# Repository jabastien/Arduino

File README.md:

# Arduino
This GitHub repo is dedicated to Arduino projects.

<H1>
https://www.arduino.cc/
<H1>

<h3>
https://www.arduino.cc/en/Reference/HomePage
</h3>

<h3>Artificial Candle</h3>
https://create.arduino.cc/projecthub/laserbrain/arduino-controlled-artificial-candle-lights-65a46d

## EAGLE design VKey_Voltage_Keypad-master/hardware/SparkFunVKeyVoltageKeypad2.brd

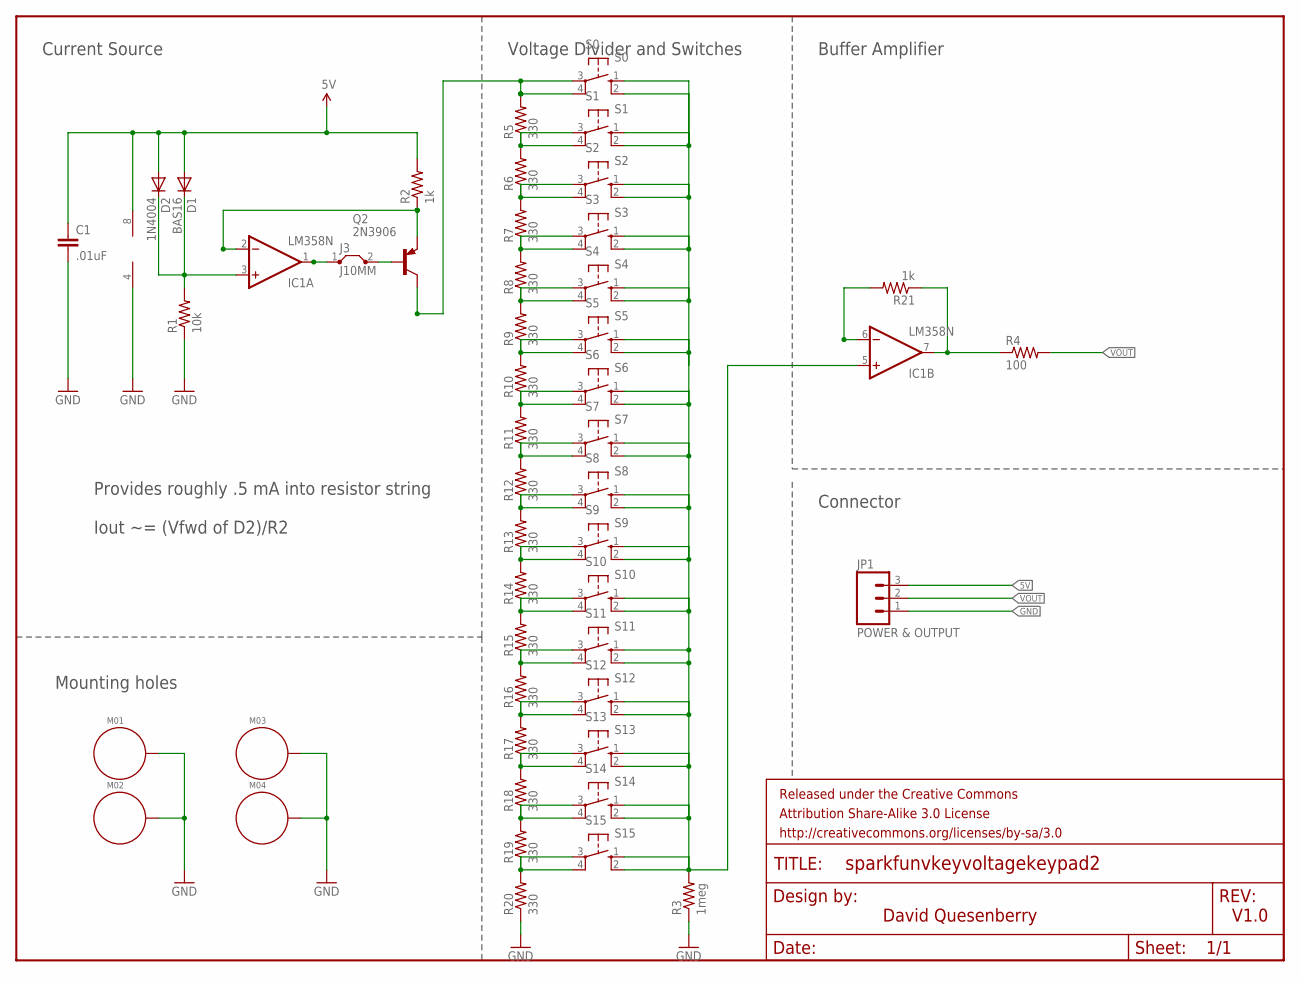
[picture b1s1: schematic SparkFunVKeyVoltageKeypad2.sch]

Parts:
C1: .01uF; 0603-CAP
D1: BAS16; SOD-323
D2: 1N4004; DO41-10
FRAME1: FRAME-LETTER; CREATIVE_COMMONS
IC1: LM358N; DIL08
J3: J10MM; 10
JP1: POWER & OUTPUT; 1X03_NO_SILK
M01, M02, M03, M04: STANDOFF_ELECTRICAL; STANDOFF-ELECTRICAL
Q2: 2N3906; TO92
R1: 10k; 0603-RES
R2, R21: 1k; 0603-RES
R3: 1meg; 0603-RES
R4: 100; 0603-RES
R5, R6, R7, R8, R9, R10, R11, R12, R13, R14, R15, R16, R17, R18, R19, R20: 330; 0603-RES
S0: S0; B3F-10XX
S1: S1; B3F-10XX
S2: S2; B3F-10XX
S3: S3; B3F-10XX
S4: S4; B3F-10XX
S5: S5; B3F-10XX
S6: S6; B3F-10XX
S7: S7; B3F-10XX
S8: S8; B3F-10XX
S9: S9; B3F-10XX
S10: S10; B3F-10XX
S11: S11; B3F-10XX
S12: S12; B3F-10XX
S13: S13; B3F-10XX
S14: S14; B3F-10XX
S15: S15; B3F-10XX

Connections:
5V: C1.1, D1.2 (A), D2.A, IC1.8 (V+), JP1.3, R2.2
GND: C1.2, IC1.4 (V-), JP1.1, M01.P1, M02.P1, M03.P1, M04.P1, R1.1, R3.1, R20.1
unnamed: D1.1 (C), D2.C, IC1.3 (+IN), R1.2
unnamed: J3.2, Q2.2 (B)
unnamed: IC1.5 (+IN), R3.2, S0.1 (S), S0.2 (S1), S1.1 (S), S1.2 (S1), S2.1 (S), S2.2 (S1), S3.1 (S), S3.2 (S1), S4.1 (S), S4.2 (S1), S5.1 (S), S5.2 (S1), S6.1 (S), S6.2 (S1), S7.1 (S), S7.2 (S1), S8.1 (S), S8.2 (S1), S9.1 (S), S9.2 (S1), S10.1 (S), S10.2 (S1), S11.1 (S), S11.2 (S1), S12.1 (S), S12.2 (S1), S13.1 (S), S13.2 (S1), S14.1 (S), S14.2 (S1), S15.1 (S), S15.2 (S1)
unnamed: R14.1, R15.2, S10.3, S10.4 (P1)
unnamed: IC1.2 (-IN), Q2.3 (E), R2.1
unnamed: Q2.1 (C), R5.2, S0.3, S0.4 (P1)
unnamed: R5.1, R6.2, S1.3, S1.4 (P1)
unnamed: R6.1, R7.2, S2.3, S2.4 (P1)
unnamed: R7.1, R8.2, S3.3, S3.4 (P1)
unnamed: R8.1, R9.2, S4.3, S4.4 (P1)
unnamed: R9.1, R10.2, S5.3, S5.4 (P1)
unnamed: R10.1, R11.2, S6.3, S6.4 (P1)
unnamed: R11.1, R12.2, S7.3, S7.4 (P1)
unnamed: R12.1, R13.2, S8.3, S8.4 (P1)
unnamed: R13.1, R14.2, S9.3, S9.4 (P1)
unnamed: R19.1, R20.2, S15.3, S15.4 (P1)
unnamed: IC1.7 (OUT), R4.1, R21.1
unnamed: IC1.6 (-IN), R21.2
unnamed: R15.1, R16.2, S11.3, S11.4 (P1)
unnamed: R16.1, R17.2, S12.3, S12.4 (P1)
unnamed: R17.1, R18.2, S13.3, S13.4 (P1)
unnamed: R18.1, R19.2, S14.3, S14.4 (P1)
unnamed: IC1.1 (OUT), J3.1
VOUT: JP1.2, R4.2

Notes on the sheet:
V1.0
Current Source
Buffer Amplifier
Mounting holes
Voltage Divider and Switches
Connector
Provides roughly .5 mA into resistor string
Iout ~= (Vfwd of D2)/R2
David Quesenberry

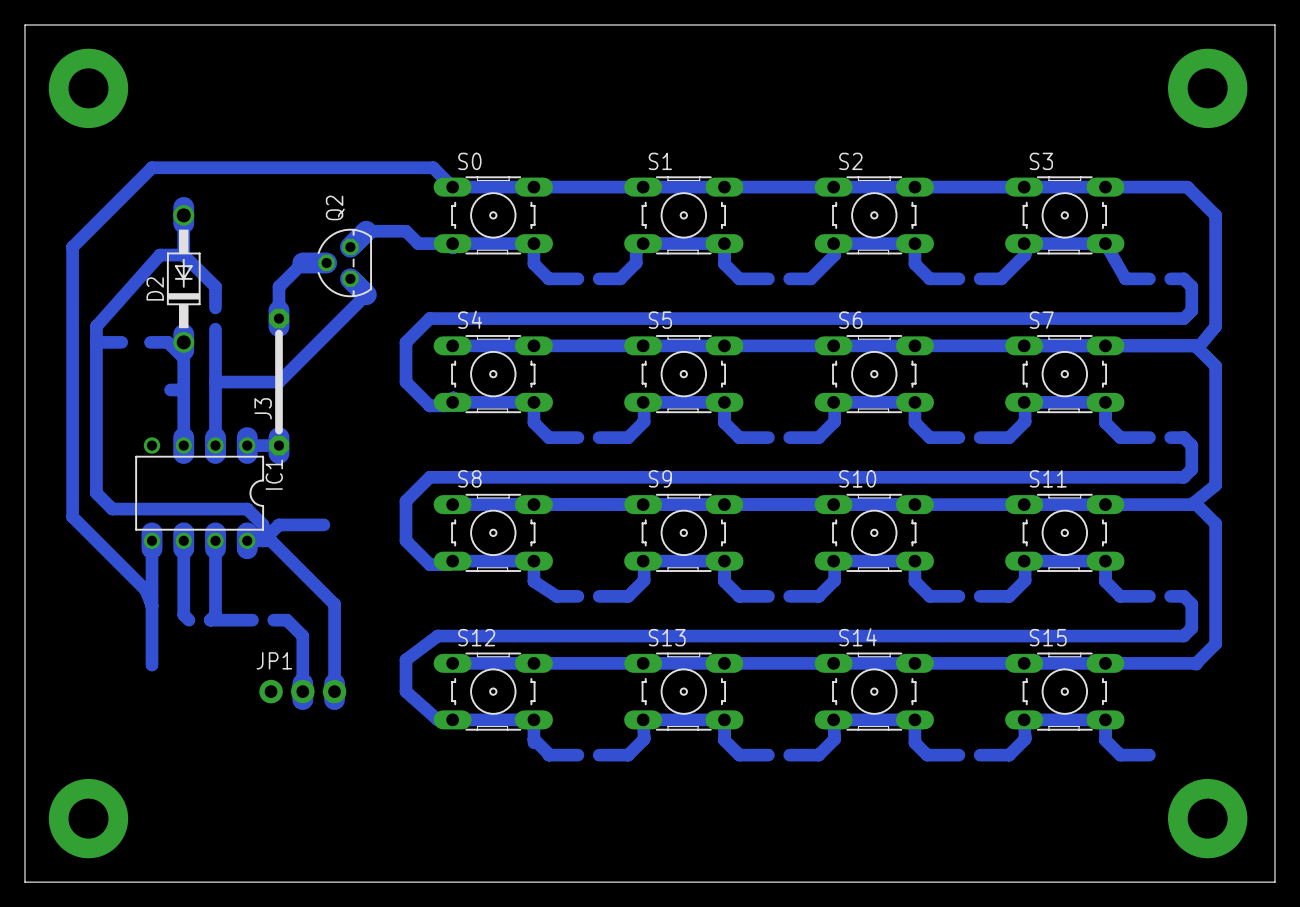
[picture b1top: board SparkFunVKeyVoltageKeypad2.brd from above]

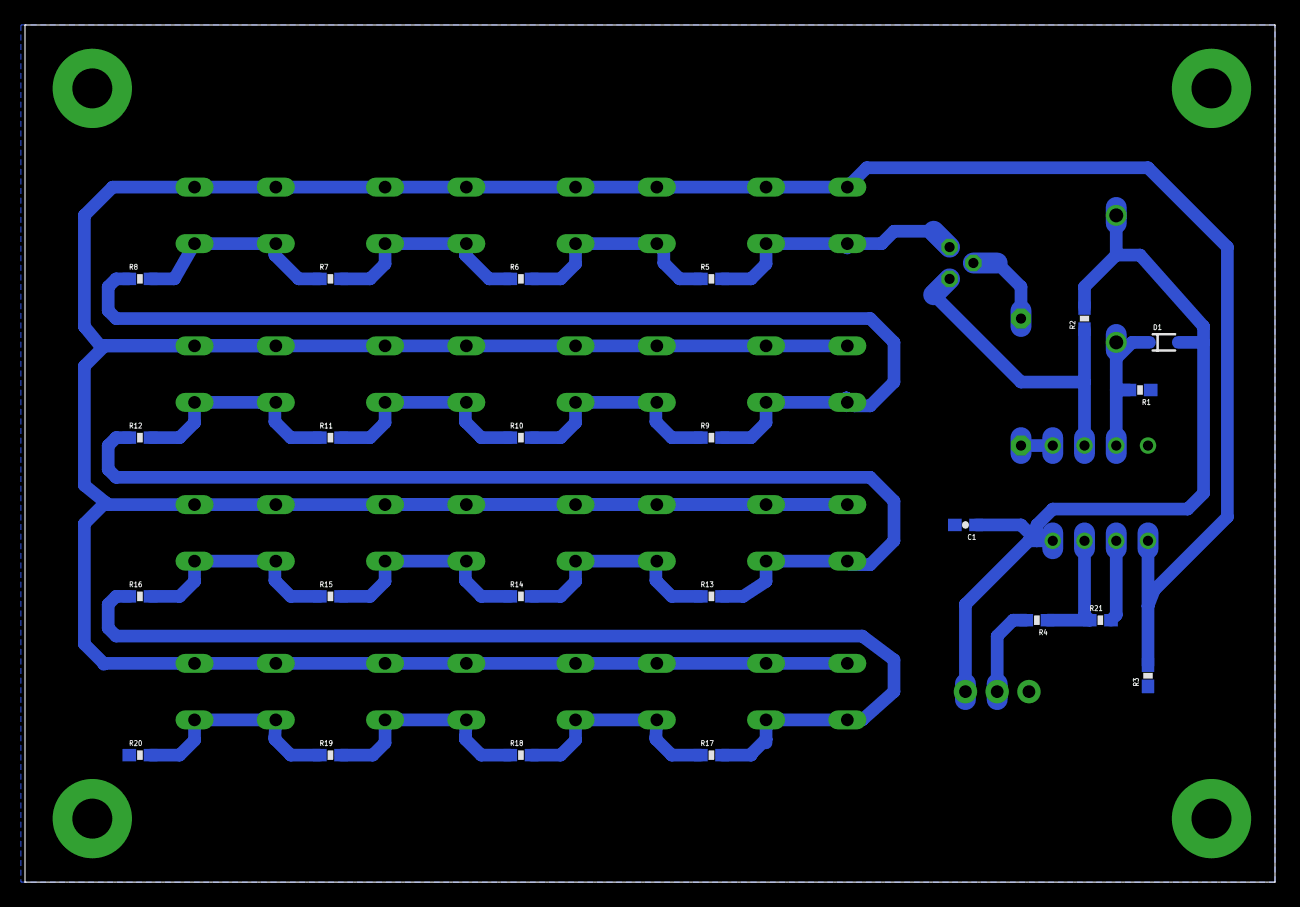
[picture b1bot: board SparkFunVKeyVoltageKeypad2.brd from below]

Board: 2 copper layers, 100.0 x 68.6 mm, 49 parts (23 on the bottom side), 26 nets.

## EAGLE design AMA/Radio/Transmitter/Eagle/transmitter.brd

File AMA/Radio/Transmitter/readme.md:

# Arduino Nano Transmitter

## Menus
| Startup |  
| ----- | 
| Name           | 
| Version        | 
| Voltage: xx.xxV | 
| QBytes-World   | 

| Main |  
| ----- | 
| Flight Time MM:SS|
| Mode: xxxxxxxxxxx| 
| Message: Xxxxxx (Warn or Error)| 
| Voltage: xx.xxV | 
| FPS xxxx GPS xxx| 
| Channel xxx Drop/Sec xxx|
| >Transmitter   | 
| >Model   | 

| >Transmitter |  
| ----- | 
| >Channel | 
| >EXPO    | 
| >Curves  | 
| >Setup   | 

| >>Transmitter Channel|  
| -----            | 
| >Scan for Open  | 
| >Channel Select | 

| >>Transmitter EXPO|  
| ----- | 
| per channel (10%-190%)  | 

| >>Transmitter Curves|  
| ----- | 
| per channel (Ramp/Sin)  | 

| >>Transmitter Setup|  
| ----- | 
| Min/Max controls | 
| Reverse surfaces (base on min/max movement)| 
| Button Ranges (press each for value) | 
| Battery (Set size in volts) | 
| >Reset Factory | 

| >Model |  
| ----- | 
| >Dip Switches (reverses)| 
| >PID - Roll   | 
| >PID - Pitch   | 
| >PID - YAW   | 

| Switches |  
| ----- | 
| S1a - Takeoff| 
| S1b - Land   | 
| S1c - ????   | 
| S2a - Sandbox     (Holds pilot to range of x meters and altitude)| 
| S2b - Barometer   (throttle sets altitude (0-400 feet)| 
| S2c - Manual   | 
| S3a - Follow-me |
| S3b - |
| S3c - |
| S4a -   | 
| S4a - Mission  | 
| S4a - Return Home   | 

| Mode |  
| ----- | 
| ??is this not the switches?? | 

|12345678901234567890|

### Arduino Nano Pinouts

| Connect |  Pin  | Pin   | Connect |
| ----- | ------ | ------ | ------ |
| Bluetooth RX     | TX     | Vin   | 7-12VDC  |
| Bluetooth TX     | RX     | Gnd   | Gnd      |
| Pull-up          | Reset  | Reset | Pull-up  |
| Gnd              | Gnd    | 5v0   | 5v0 Out  |
| Buzzer/LED       | D2     | ADC7  | CD4052-Y |
| CD4051/CD4052-A  | D3     | ADC6  | CD4052-X |
| CD4051/CD4052-B  | D4     | SDC   | LCD SDC  |
| CD4051       -C  | D5     | SDA   | LCD SDA  |
| CD4051 #1 (Switch)| D6    | ADC3  | Role     |
|?CD4051 #2 (Trims)?| D7     | ADC2  | Pitch    |
|?CD4051 #3 (Menu) ?| D8     | ADC1  | Yaw      |
| Nrf24 - CE       | D9     | ADC0  | Throttle |
| Nrf24 - CSN      | D10    | Aref  | 5v0      |
| Nrf24 - MOSI     | D11    | 3v3   | N/C      |
| Nrf24 - MISO     | D12    | D13   | Nrf24 - CSN|

### NRF24 with PA and antenna Pinouts
| Arduino Pin |  NRF24 Pin  | NRF24 Pin   | Arduino Pin |
| ----- | ------ | ------ | ------ |
| GND   | GND    | VCC    | 3v3    |
| D9    | CE     | CSN    | D10    |
| D13   | SCK    | MOSI   | D11    |
| D12   | MISO   | IRQ    | N/C    |

> **Transmitter performance tuned setup**
> - AutoAck = false 
> - Max power 
>   - setPALevel( RF24_PA_MAX ) ; 
> - Min speed (for better range I presume)
>   - setDataRate( RF24_250KBPS ) ; 
> - 8 bits CRC
>   - setCRCLength( RF24_CRC_8 ) ; 
> - Disable dynamic payloads 
>   - write_register(DYNPD,0); 
> - increase the delay between retries & # of retries 
>   - setRetries(15,15);
> - Add capacitor to board.

> - Modify pipeOut to be unique for your codebase

Here is what I'm using:
1. Power supply:

      a. decouple your LDO properly(it needs 1-2uF ceramic, not 100n + 100u electrolytic!). 
      
      b. use a decoupling cap next to the module (1-2 uF ceramic).
      
      c. in-line choke (coil) for 3v3 line.
      
2. Use a linear instead of a switching power supply
3. Don’t use polling over SPI to check if there is a received packet like most of the libs out there do. This increases the noise. Use the IRQ pin.
4. 250Kbps does wonders
5. Careful about cheap connectors, solder it if you can.
6. A big ground near the module is preferred, like putting it in a metal box with a good contact to antenna ground.
7. Don’t use long wires to the module, specially cheap stuff.

See here: http://www.electrobob.com/bad-wires/

test

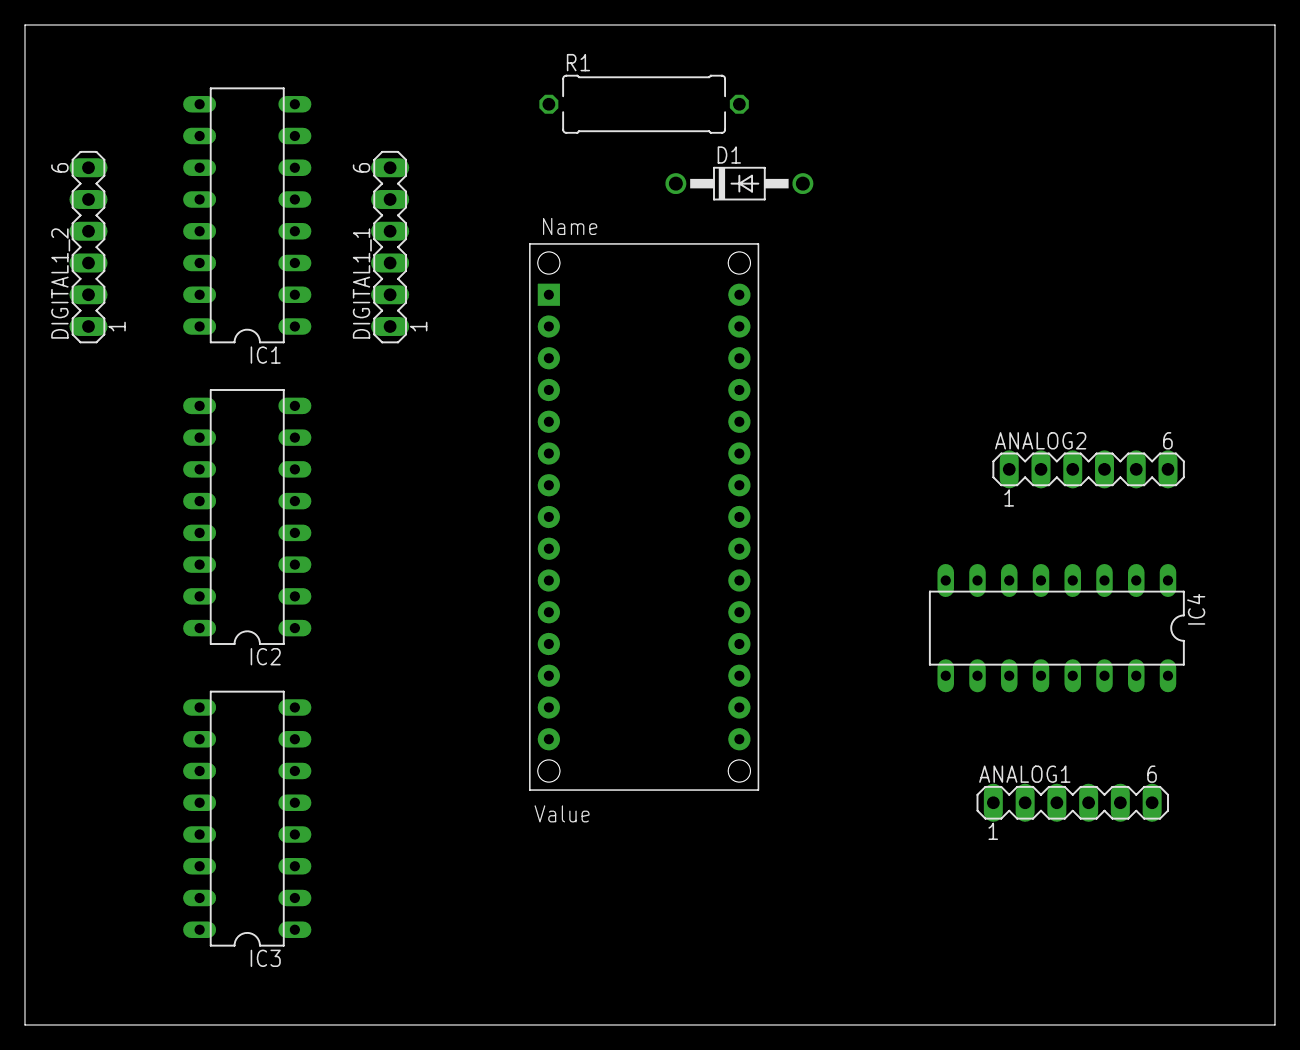
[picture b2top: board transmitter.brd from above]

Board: 2 copper layers, 100.0 x 80.0 mm, 11 parts (0 on the bottom side), 24 nets, no tracks yet.

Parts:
ANALOG1, ANALOG2: MA06-1
D1: 1N4004; DO41-10
DIGITAL1_1, DIGITAL1_2: MA06-1
IC1, IC2, IC3: 4051N; DIL16
IC4: 4052N; DIL16
R1: P0613/15
U$1: ARDUINONANO; PDIP-32

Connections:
GND: IC1.6, IC1.7, IC1.8, IC2.6, IC2.7, IC2.8, IC3.6, IC3.7, IC3.8, IC4.6, IC4.7, IC4.8, U$1.GND, U$1.GND1
unnamed: IC4.13, U$1.A7
unnamed: IC4.3, U$1.A6
unnamed: IC1.11, IC2.11, IC3.11, IC4.10, U$1.D3
unnamed: IC1.10, IC2.10, IC3.10, IC4.9, U$1.D4
unnamed: IC1.9, IC2.9, IC3.9, U$1.D5
unnamed: IC1.3, U$1.D6
unnamed: IC2.3, U$1.D7
unnamed: IC3.3, U$1.D8
unnamed: D1.C, U$1.VIN
unnamed: R1.1, U$1.RESET
unnamed: ANALOG1.4, IC4.12
unnamed: ANALOG1.3, IC4.14
unnamed: ANALOG1.2, IC4.15
unnamed: ANALOG1.1, IC4.11
unnamed: ANALOG2.4, IC4.1
unnamed: ANALOG2.3, IC4.5
unnamed: ANALOG2.2, IC4.2
unnamed: ANALOG2.1, IC4.4
unnamed: DIGITAL1_2.1, IC1.13
unnamed: DIGITAL1_2.2, IC1.14
unnamed: DIGITAL1_2.3, IC1.15
unnamed: DIGITAL1_2.4, IC1.12
VDD: IC1.16, IC2.16, IC3.16, IC4.16, U$1.+5V

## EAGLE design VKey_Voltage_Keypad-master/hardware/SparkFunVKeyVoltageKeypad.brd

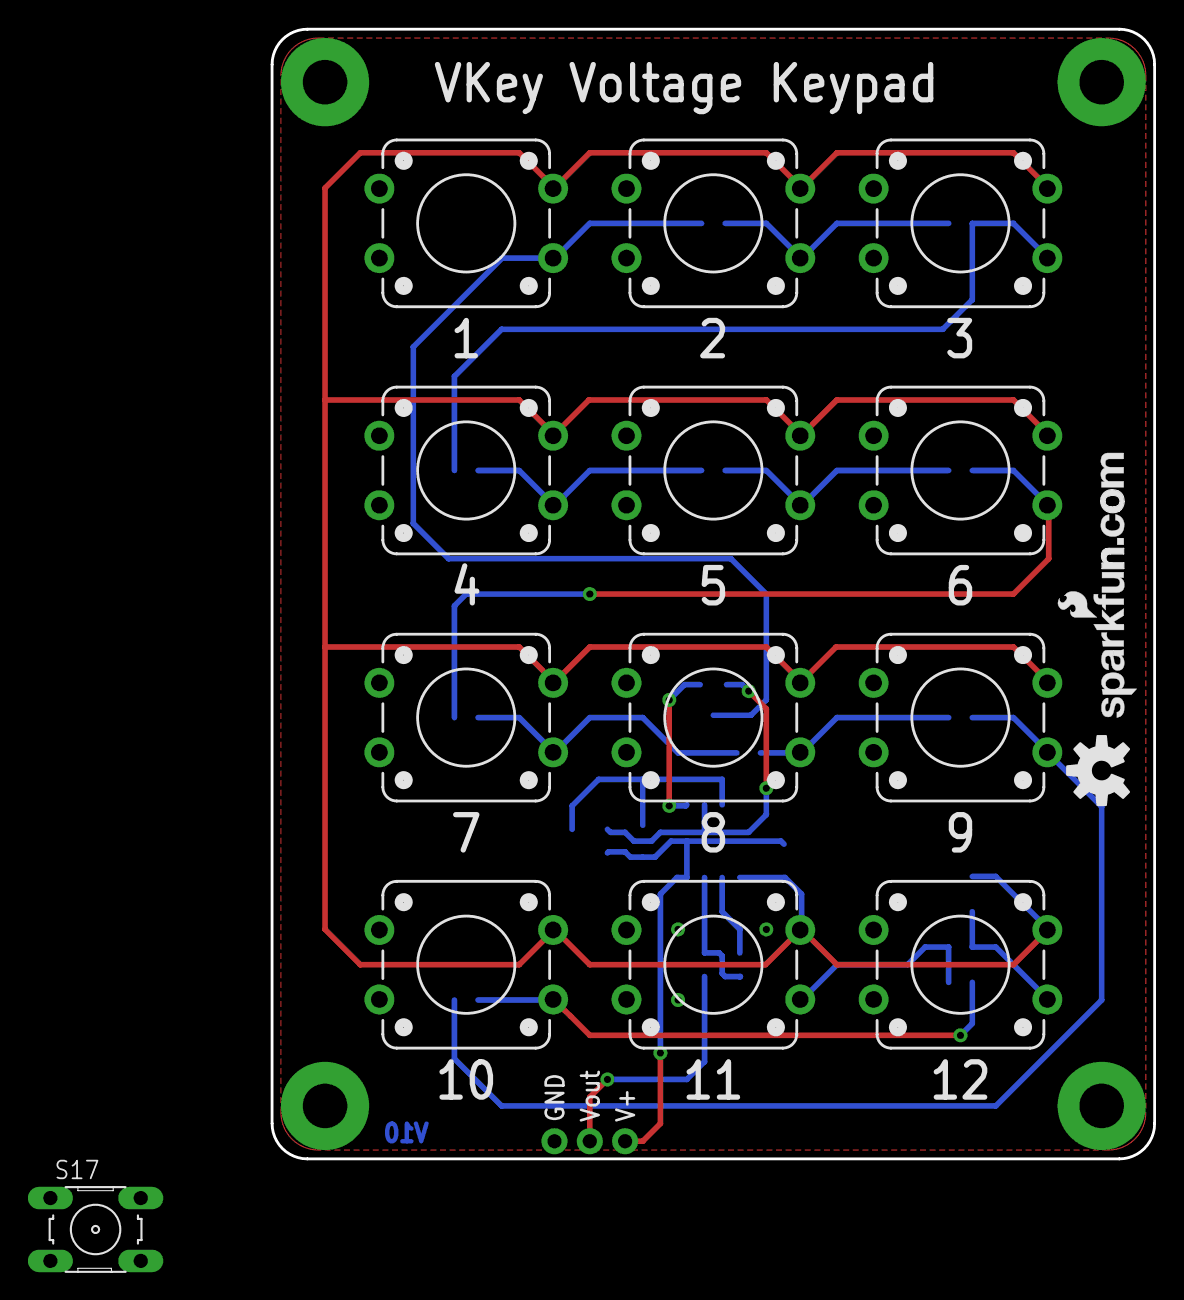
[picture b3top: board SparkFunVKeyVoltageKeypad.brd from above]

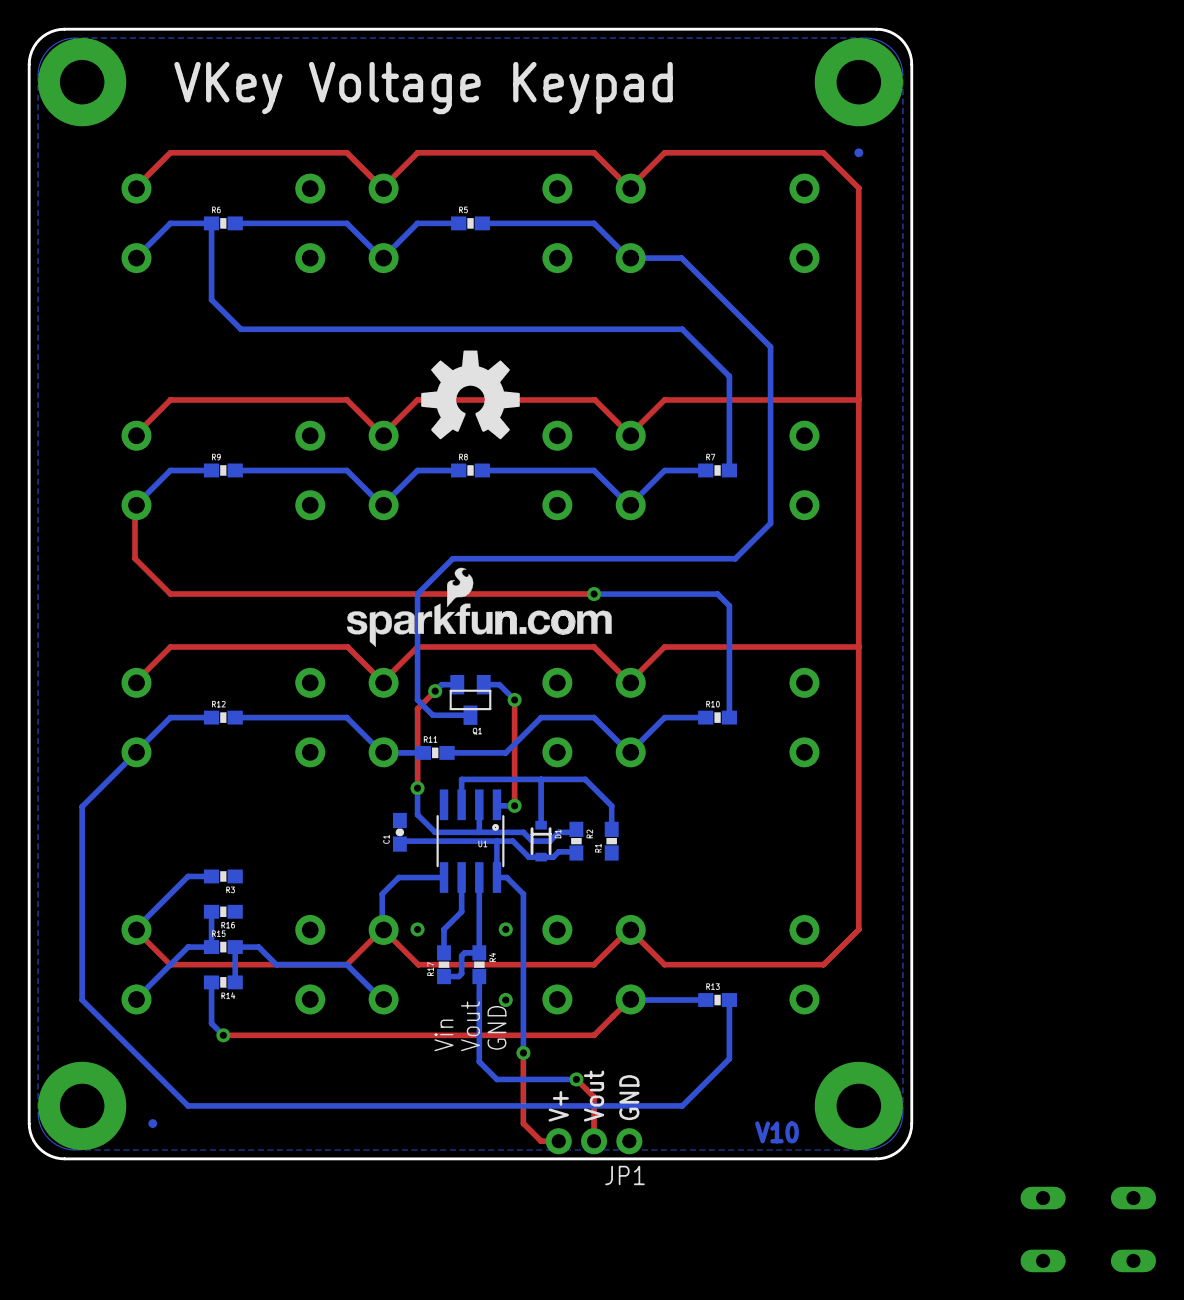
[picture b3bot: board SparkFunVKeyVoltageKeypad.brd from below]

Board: 2 copper layers, 63.5 x 81.3 mm, 46 parts (26 on the bottom side), 21 nets.

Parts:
C1: .01uF; 0603-CAP
D1: BAS16; SOD-323
FID1, FID2: FIDUCIALUFIDUCIAL; MICRO-FIDUCIAL
FRAME1: FRAME-LETTER; CREATIVE_COMMONS
JP1: POWER & OUTPUT; 1X03_NO_SILK
LOGO1, LOGO2: LOGO-SFENEW; SFE-NEW-WEBLOGO
LOGO3: OSHW-LOGOM; OSHW-LOGO-M
LOGO4: OSHW-LOGOL; OSHW-LOGO-L
Q1: MMBT3906; SOT23
R1: 10k; 0603-RES
R2, R17: 1k; 0603-RES
R3: 1meg; 0603-RES
R4: 100; 0603-RES
R5, R6, R7, R8, R9, R10, R11, R12, R13, R14, R15, R16: 330; 0603-RES
S1, S2, S3, S4, S5, S6, S7, S8, S9, S10, S11, S12: SWITCH-MOMENTARY-212MM; TACTILE-PTH-12MM
S13, S14, S15, S16: STANDOFF_ELECTRICAL; STANDOFF-ELECTRICAL
S17: B3F-10XX
U1: LMV358; SO08

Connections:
5V: C1.1, D1.2, JP1.3, R2.2, U1.8
GND: C1.2, JP1.1, R1.1, R3.1, R16.1, S13.P1, S14.P1, S15.P1, S16.P1, U1.4
unnamed: D1.1, R1.2, U1.3
unnamed: Q1.1, U1.1
unnamed: R3.2, S1.3, S2.3, S3.3, S4.3, S5.3, S6.3, S7.3, S8.3, S9.3, S10.3, S11.3, S12.3, U1.5
unnamed: R14.1, R15.2, S11.1
unnamed: Q1.2, R2.1, U1.2
unnamed: Q1.3, R5.2, S1.1
unnamed: R5.1, R6.2, S2.1
unnamed: R6.1, R7.2, S3.1
unnamed: R7.1, R8.2, S4.1
unnamed: R8.1, R9.2, S5.1
unnamed: R9.1, R10.2, S6.1
unnamed: R10.1, R11.2, S7.1
unnamed: R11.1, R12.2, S8.1
unnamed: R12.1, R13.2, S9.1
unnamed: R13.1, R14.2, S10.1
unnamed: R15.1, R16.2, S12.1
unnamed: R4.1, R17.1, U1.7
unnamed: R17.2, U1.6
VOUT: JP1.2, R4.2

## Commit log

2017-08-23 restore
    restore damaged repo
2017-08-23 AMA add
    AMA add
2017-08-23 Still recovering
2017-08-23 Set theme jekyll-theme-dinky
2017-08-23 Adding MD readme
2017-08-23 Updatine Readme
2017-08-24 CD4051 & CD4052 working
    Completed the updates to reduce code size.
    Need to review performance.
2017-08-24 Easier to read CD4052
2017-08-26 Documentation
    Documentation for Github page
2017-08-26 test md
2017-08-26 MD file still
2017-08-27 QBytes_library
    Remove library compile warning
2017-08-27 Removing EXE files.
    Removing EXE files.
2017-08-31 nFR2401 1.3
    Updated nFR2401 to 1.3
2017-09-01 Added TPS, LCD and 405x
    TPS ~ 245
    (1) 4051 - tested
    (1) 4052 - tested
    Display volts fake pin (joystick)
2017-09-01 Main Menu
    Updated main menu with clock, volts, channel & TPS.
2017-09-01 Eagle schema
2017-09-01 Reduce to 3 autoroutes
2017-09-01 Working on it
2017-09-11 Transmitter PCB
2017-11-08 Updating Transmitter
    Working on:
    - volts
    - shunt
    - menu
    - menu - first time run
2017-11-08 Consolidating code
    Code cleanup
2017-11-09 Working on menu
    Array is working, need to understand how to step through
2017-11-10 Menu work
    Starting to work. Able to see multi levels.
2017-11-10 Menu tweak
    last one tonight.
2017-11-19 Keypad Library
    Create Keypad library
2017-11-19 Better control
    Numbers are more consistant
2017-11-19 Added Protected
    Added comment section for protected vars
2017-11-19 Keypad working consistantly
    Good values returned and with repeat.
2017-11-19 Compacting
    Code cleanup and remove of default values, reduced code from 2864 to
    2658 bytes and variables from 250 to 244.
2017-11-19 Comment cleanup
    Comment cleanup
2017-11-19 Removed my test
    Testing direct updates to GIT vs local for Sync
2017-11-19 Logic change
    No need to init input if looping above.
2017-11-19 Added KeyPad
    Also cleaned up some code.
2017-11-20 Organizing code
    Cleanup, trying to understand code size of 14,456 & 1603
2017-11-20 Working on flow and menu
    Found bug in menu, if line > menuOption size. Added menuSize for line
    test.
2017-11-20 Added custom chars
    This can be used for battery or signal strength levels.
2017-11-22 Menu flow, functions and number editor.
    Menu flow, functions and number editor.
2017-11-24 Menu working
    Menu was working on Octal. Needed to remove leading zeroes. Remove
    const byte for SIZE, just pass it... Reserved 255 and 000. 001 =
    mainmenu, 255 if for functions. A lot of print statements for debug
    (need to remove/comment them).
2017-11-24 Starting breakout of classes.
2017-11-25 Working on formatting then edit numbers.
2017-11-25 menu?
2017-11-25 Done for the night
    UInt and Int appear to be working
2017-11-26 Working on display formatter.
2017-11-26 Moving globals to FLASH RAM
    (F("string"))
2017-11-26 Working on Display and Menu
    Display all resistors and volts working
    Menu carrot and blink adjusted.
2017-11-26 Moving around to correct locations
    concatBytesPGM & concatBytesPGMSTR
2017-11-27 working on x253
2017-11-27 Hide Sys Volt as resistors not set yet
2017-11-28 Seperating code
2017-11-28 Bad build, can't revert.
2017-11-28 what a mess
2017-11-28 commit for refert
    commit for refert
2017-11-28 Revert "commit for refert"
    This reverts commit 24fb95562bf3e49d699b109e4220b1de1c04a411.
2017-11-28 Revert "Bad build, can't revert."
    This reverts commit 0159ab18d00fd8752035bdc98b548707c71bb7df.
2017-11-28 Revert "commit"
    This reverts commit 7e02a5ba40f62e67841347020a495ee1b646f430.
    # Conflicts:
    # AMA/Radio/Transmitter/Display.cpp
    # AMA/Radio/Transmitter/Display.h
    # AMA/Radio/Transmitter/types.h
2017-11-28 Compiiling again
2017-11-29 Global error resolved?
2017-11-29 Catching up since the crash...
2017-11-29 DisplayInfo struct now working with Display
2017-12-10 Cleanup of the Display
    Class knew too much about other things, not any more.
2017-12-10 Done for the night
2017-12-12 Broke out Menu to it's own class.
    16170 bytes (52%) of program storage space.
    Global variables use 1268 bytes (61%) , leaving 780 bytes for local
    variables.
2017-12-13 Still splitting Transmitter with Data
2017-12-13 Comments
    Done for the night
2017-12-16 Passing Data.cpp as a point to DataStore and Menu
2017-12-16 Clean-up
2017-12-16 Clean-up 2
2017-12-17 Passing pointers
2017-12-17 works but not a clean answer.
    Can this be completed in Data as a method by type
2017-12-17 adjValue working
    Need to breakout to 8, 16, 32 & un-Signed/Signed methods.
2017-12-17 Working on menu.
2017-12-17 x251 almost working
2017-12-17 Added DEFINES for KEYPRESS and debugging info
2017-12-18 Moving to SRAM
2017-12-18 INC/DEC working, not well, but working
2017-12-18 Rebuilding menu code / cleanup
2017-12-18 Still working on menu
    Need to call the key press rtn instead of hardcoding menu change
2017-12-18 Moved to new menu
    Found bug with FUNCTION, not loading options for them any more
2017-12-18 Menu working better.
2017-12-18 Pretty
    Still a lot to do.
2017-12-18 Still a ways to go on EDIT
2017-12-19 Starting the use of Edit.cpp
2017-12-19 Tweak for test.
2017-12-20 Looping and counting.
    Need to turn it into a CLASS
2017-12-20 Found bug with a MASK that starts with '#'.
    Expo will be 0 if move right from 0 (far right).
2017-12-21 Edit working
    Edit working with a lot of Println, need to clean up.
2017-12-21 Commented most Prints
2017-12-21 Still working on Edit.
    Added hard coded uint32 POW (bug in float for POW).
2017-12-21 good enough
2017-12-22 Edit almost done, need to implement KeyPress
2017-12-22 251 working with Mask and Data change
2017-12-22 Doing cleanup of Menu and Display
2017-12-22 Menus 254 - 248 look good
    // Starting [click (select) out to 254]
    // Shunt ohms
2017-12-23 New add method, 2 bytes instead of 4
2017-12-23 Test for overflow MIN/MAX value for uInt16Adj
2017-12-23 Align menu to groups
    000-000 = Reserved
    001-049 = Transmitter
    050-099 = Models
    100-149 = System
    150-199 = Init/Startup
    200-154 = Functions
2017-12-24 todo list
2017-12-24 todo's 2
2017-12-24 Added 5.1 diode to board and moved to Transmitter folder.
2017-12-24 One Switch working
2017-12-24 Done for the day...working on "outputBinary"
2017-12-25 Finish Switches
2017-12-26 Still working on menu
2017-12-26 Missed check in
2017-12-27 Controls Range working.
2017-12-27 Reducing footprint
    Move mapRange into the Struct
2017-12-27 Update FPS and _data to data
    Main menu FPS is 575
2017-12-27 Organized/Reset todo.h list
    disabled sound on keypad
2017-12-28 May be a bug in this....
2017-12-28 Size adj
    59% 18,246 / 1,088 53%
2017-12-28 missed checkin
2017-12-29 Building menues
2017-12-29 Working upto MainMenu
    Corrected bug of missing screens. Was doing keypress twice. (Keypress
    and Screen refresh). Changed Screen refresh to NOKEY.
2017-12-29 formatting
2017-12-29 Cleanup
2017-12-29 Fixed Carrot, still needs more work
2017-12-31 Working on menus
2018-01-01 Menues, Bug & SW/Btns
    X - build menus
    = Trans
    = Model
    = System
    X - bug in menu, able to arrow down one (1) when no items are available
    (Bug no longer found)
2018-01-01 Cleanup ERR:
2018-01-01 Added Aux, Volts & menu options
2018-01-02 Aux working,
2018-01-03 CntrlHome working
2018-01-04 Reduce size from 73% to 68%
2018-01-06 Factory Reset working
2018-01-07 Using EEPROM and isVersionMatch to skip INIT if already run.
2018-01-15 ConstantCurrent
    DummyLoad check-in
2018-01-15 Simplify
2018-01-15 Still working on the CC_DL
2018-01-20 Updated wires again.
2018-01-20 Ready to etch???
2018-02-17 Enable Radio
2018-02-17 Version
2019-01-26 sync
2019-02-23 Created the power Supply
2019-02-23 Samples
2019-02-24 Corrected roundeing
2019-04-06 Constant Current
    and Adafruit updates
2019-10-23 New pumkin code and cleanup of old comments

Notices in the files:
parts and their libraries:
SparkFun-Aesthetics: Licensing: CC v3.0 Share-Alike You are welcome to use this library for commercial purposes.
SparkFun-Aesthetics: Released under the Creative Commons Attribution Share-Alike 3.0 License
SparkFun-Aesthetics: http://creativecommons.org/licenses/by-sa/3.0
